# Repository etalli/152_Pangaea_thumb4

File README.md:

2023/02/05
MIT LICENSE

# Pangaea RI 1.2 Extension
This is a version of the Pangaea RI 1.2 thumb modules

## 4-key rightmost key deleted (right most key cut)

This is a version of the Pangaea RI 1.2 thumb module with the rightmost key deleted.

The original thumb module can be made to 4-key version by cutting each of the three PCBs, but this is not only time-consuming but also potentially injurious.

|  Parts  |  Picture  |
| ---- | ---- |
| Top Plate |   |
| PCB |  |
| Bottom Plate |  |

*Note: SH connector can be used only for the left side, connector with x mark won't work.

## 4-key rightmost key deleted (leftt most key cut)

This is a version of the Pangaea RI 1.2 thumb module with the leftmost key deleted.

### Changes

The changes are basically just removing the rightmost key from the standard PCB. And for the leftmost standoff on the PCB, the space has been filled in to support the PCB from below. The PCB can now be supported using M1.4 size screws.

## 8-key thumb module with arrow keys

8-key thumb moudule with arrow keys. (test sample)

|  Parts  |  Picture  |
| ---- | ---- |
| Top Plate |   |

## History
* 2023/02/18 External shape changed to the same state as when it was cut cleanly; Top, PCB and Bottom size match confirmed.
* 2023/10/16 thumb8-arrowkey module added.

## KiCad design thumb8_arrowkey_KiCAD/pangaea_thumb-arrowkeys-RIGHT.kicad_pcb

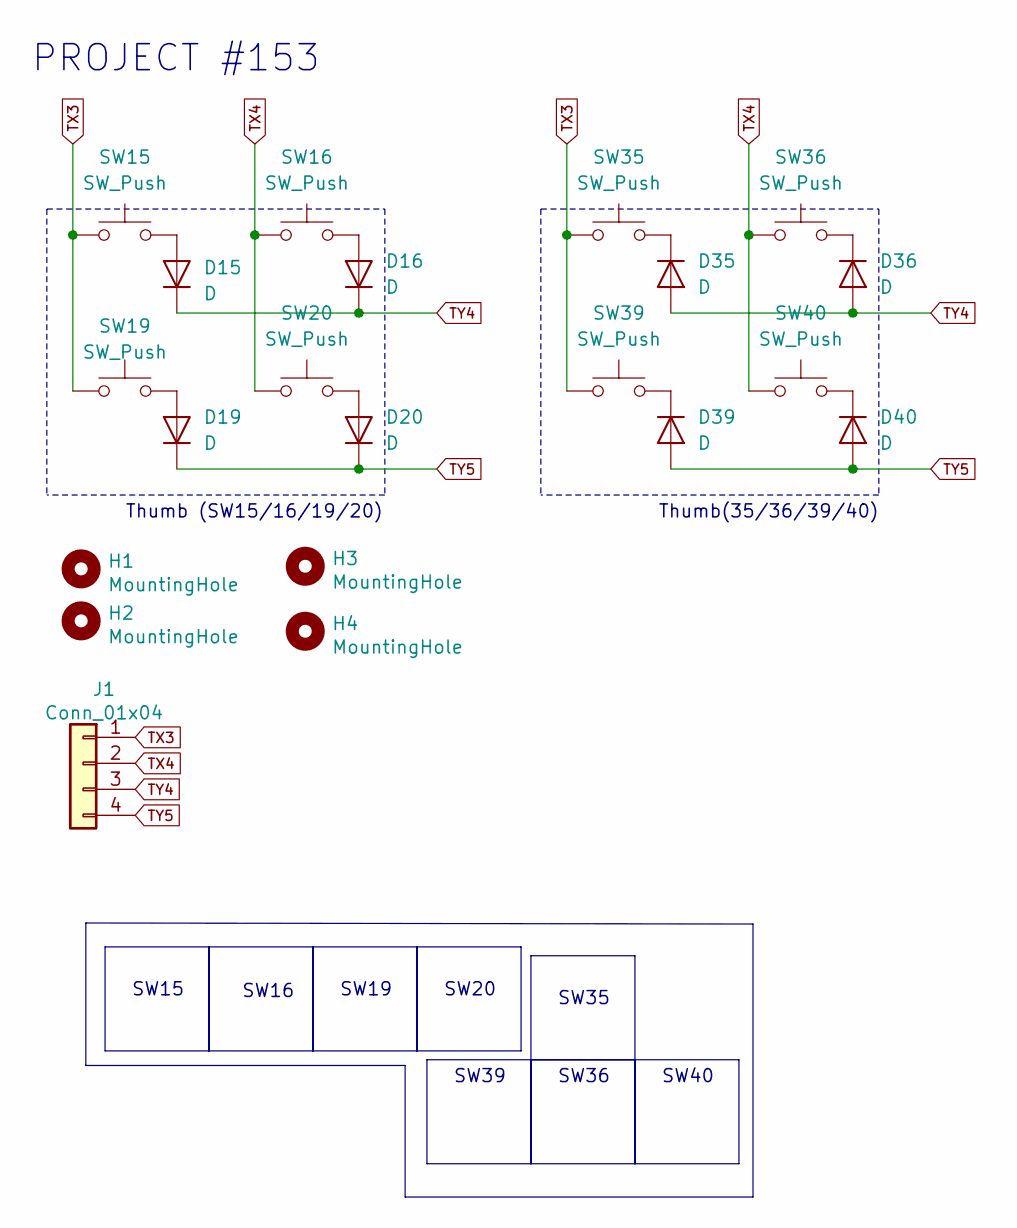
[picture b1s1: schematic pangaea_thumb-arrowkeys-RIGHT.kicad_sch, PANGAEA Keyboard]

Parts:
D15, D16, D19, D20, D35, D36, D39, D40: D; diode_TH_SMD_rev3
H1, H2, H3, H4: MountingHole; M2_Nut_Hole_rev2
J1: Conn_01x04; JST_SH_BM03B-SRSS-TB_1x04-1MP_P1.00mm_Vertical
SW15, SW16, SW19, SW20, SW35, SW36, SW39, SW40: SW_Push; CherryMX_Choc_Hotswap_rev9_test

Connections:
unnamed: D15.2 (A), SW15.2
unnamed: D16.2 (A), SW16.2
unnamed: D19.2 (A), SW19.2
unnamed: D20.2 (A), SW20.2
unnamed: D35.1 (K), SW35.2
unnamed: D36.1 (K), SW36.2
unnamed: D39.1 (K), SW39.2
unnamed: D40.1 (K), SW40.2
TX3: J1.1, SW15.1, SW19.1, SW35.1, SW39.1
TX4: J1.2, SW16.1, SW20.1, SW36.1, SW40.1
TY4: D15.1 (K), D16.1 (K), D35.2 (A), D36.2 (A), J1.3
TY5: D19.1 (K), D20.1 (K), D39.2 (A), D40.2 (A), J1.4

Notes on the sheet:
SW19
Thumb(35/36/39/40)
Thumb (SW15/16/19/20)
SW39
SW20
SW35
SW16
SW40
SW36
PROJECT #153
SW15

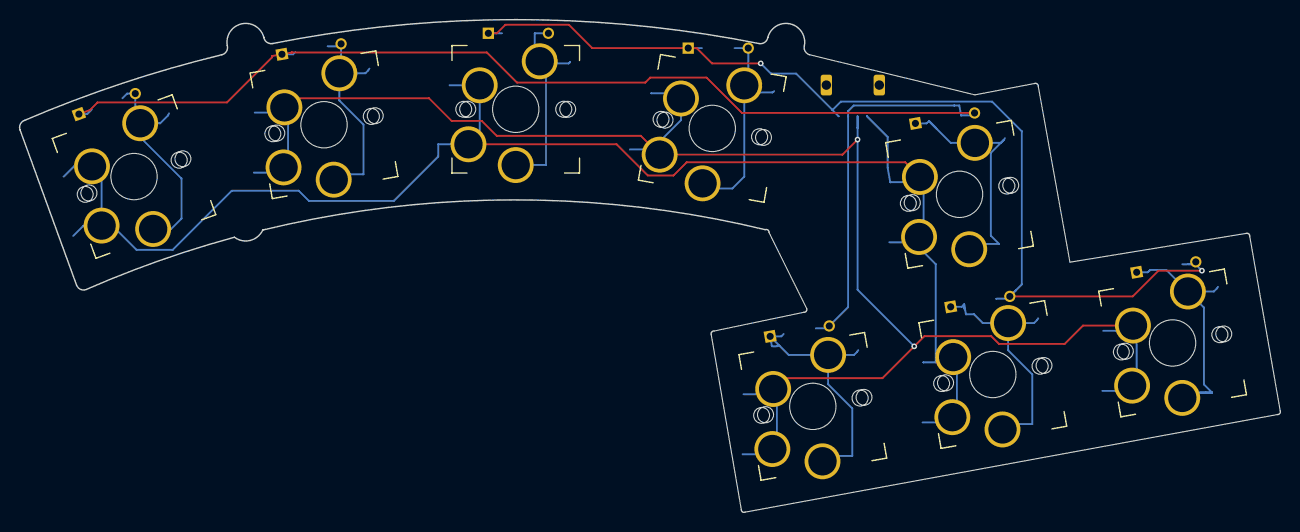
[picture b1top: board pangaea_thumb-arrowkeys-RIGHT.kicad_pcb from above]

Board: 2 copper layers, 133.4 x 52.1 mm, 21 parts (1 on the bottom side), 12 nets.

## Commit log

2023-10-15 1st commit
2023-10-16 added thumb8-arrowkeys
